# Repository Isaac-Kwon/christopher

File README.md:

# Project Christopher

앨런 튜링의 에니그마 해독기 **봄베(Bombe)** 를 재현하는 프로젝트.

소프트웨어 모델(Rust 코어 + Python 조작 인터페이스)에서 시작해 RTL, 실물까지 단계적으로 진행하고, LaTeX 보고서로 마무리한다.
재현 범위는 튜링-웰치먼 3로터 봄베와 해군 4로터(M4)까지다.

## 현재 상태

- **Phase 0 (기반): 완료.** 자료 조사, 배선표, 검증 벡터, 빌드 구성.
- **Phase 1 (소프트웨어): 동작.** 에니그마 I / M3 / M4, 메뉴 생성기, 3·4로터 봄베, 체킹 머신, 전체 탐색, Python 조작 인터페이스. 크립에서 평문까지 끝까지 해독한다.
- Phase 2 (RTL) 이후는 미착수.

전체 계획, 로드맵, 디렉토리 구조는 [docs/PLAN.md](docs/PLAN.md)에 있다.

## Quickstart

필요한 것: Rust 툴체인, Python 3.10 이상, [maturin](https://www.maturin.rs/).

### 빌드 출력 위치

이 저장소는 Dropbox 폴더 안에 있다. Dropbox가 `target/` 안의 파일을 잠가 빌드가 실패하는 문제가 실제로 발생했기 때문에, **빌드 출력과 Python 가상환경은 Dropbox 밖에 둔다.**

| 대상 | 위치 | 설정 |
|---|---|---|
| Cargo 빌드 출력 | `%LOCALAPPDATA%/christopher/target` | `.cargo/config.toml` (PC별 설정, git 제외) |
| Python 가상환경 | `%LOCALAPPDATA%/christopher/venv` | 수동 생성 |

프로젝트 폴더 안에는 가상환경을 만들지 않는다. 다른 PC에서는 `.cargo/config.toml`의 `target-dir`과 아래 경로를 그 PC에 맞게 바꾼다.

### 빌드

Python 바인딩을 가상환경에 설치한다 (Git Bash 기준, 저장소 루트에서 실행).

```bash
export VIRTUAL_ENV="$LOCALAPPDATA/christopher/venv"
$VIRTUAL_ENV/Scripts/maturin.exe develop --release
```

PowerShell에서는 `$env:VIRTUAL_ENV = "$env:LOCALAPPDATA/christopher/venv"` 뒤에 `& "$env:VIRTUAL_ENV/Scripts/maturin.exe" develop --release`.

### 시험

```bash
cargo test -p christopher-core
$VIRTUAL_ENV/Scripts/python.exe -m pytest tests
```

### 사용 예

암호문과 크립(추정 평문)에서 키와 평문을 복원한다.

```python
from christopher import Enigma, search

plain = "ANXOBERKOMMANDODERWEHRMACHTXWETTERVORHERSAGEFUERDIENORDSEEXHEUTEKLAR"
secret = Enigma("enigma-i", rotors=("III", "V", "II"), reflector="B", rings="GMC",
                positions="KDC", plugboard="AQ BZ CR DM EV FW GK HN IU JP")
cipher = secret.encrypt(plain)

# 크립 WETTERVORHERSAGEFUERDIE가 암호문의 28번째 글자(0부터)에서 시작한다고 보고 전체 로터 순서를 탐색
report = search(cipher, "WETTERVORHERSAGEFUERDIE", 28, model="enigma-i", max_edges=14)
print(report)                 # 120 wheel orders, 2109120 positions, ...
print(report.solutions[0])    # 로터 순서, 링, 시작 위치, 플러그보드, 평문
```

메뉴 작성 → 배선 → 구동 → 정지 확인 → 체킹을 단계별로 따라 하려면 노트북 [notebooks/01_crib_to_plaintext.ipynb](notebooks/01_crib_to_plaintext.ipynb)를 본다. 노트북 실행에는 `ipykernel`과 `matplotlib`이 필요하다(같은 가상환경에 설치).

M4 전체 탐색(로터 순서 1,344개, 약 6.1억 위치)의 예:

```bash
cargo run --release -p christopher-core --example full_search m4
```

## 문서

- [docs/PLAN.md](docs/PLAN.md) — 목표, 아키텍처, 로드맵, 디렉토리 구조
- [docs/reference/bombe-mechanics.md](docs/reference/bombe-mechanics.md) — 3로터 봄베의 기구와 동작 (출처 포함)
- [docs/reference/four-rotor-and-relay-bombes.md](docs/reference/four-rotor-and-relay-bombes.md) — 4로터 봄베와 릴레이식 봄베
- [report/references.bib](report/references.bib) — 참고문헌

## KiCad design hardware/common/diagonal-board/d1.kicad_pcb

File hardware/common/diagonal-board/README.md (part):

# Diagonal board, five boards (common part)

Generated KiCad 10 schematics and **placement-only** PCBs of Welchman's diagonal board, split in five boards as decided in
`docs/decisions/0002-gear-detail-decisions.md` section 9 and `hardware/common/diagonal-board.md`; connector rules from
`docs/decisions/0003-interfaces.md` (5.1 gender, 5.2 pins, 7 grounding/CHASSIS). The letter jacks live on these boards
(design brief 4.3/4.4); everything else of the menu panel is on `hardware/common/patch-panel`. Build products of the scripts, do not edit by hand.

## Design

| Board | Letters (jack columns: upper / lower) | Jacks | Junction headers | Size (placed) | Left edge on the panel |
|---|---|---:|---|---|---:|
| D1 | A B C / N O P | 12 | 3 right (edge) | 331.6 x 130 | 17.8 |
| D2 | D E F / Q R S | 12 | 3 left (gap col 1-2), 3 right (edge) | 327.6 x 130 | 351.8 |
| D3 | G H I / T U V | 12 | 3 left (gap col 1-2), 3 right (edge) | 327.6 x 130 | 681.8 |
| D4 | J K / W X | 8 | 3 left (gap col 1-2), 3 right (edge) | 217.6 x 130 | 1,011.8 |
| D5 | L M / Y Z | 8 | 3 left (gap col 1-2) | 190.5 x 130 | 1,231.8 |

Panel x is measured from the left end of the 1,440 mm bank span (`hardware/gear/layout.md` 3.9/3.10; the relay machine's panel is the
same). The five boards cover 17.8 ... 1,422.2 (1,404.5 mm, 2.4 mm air between boards, 17.8 mm free at each end).

* **Letter jack** (2 per letter, 52 in all): male D-sub 37 (`DSUB-37_Pins_Vertical..._MountingHoles`, shells through the panel), pins 1-26 =
  wire A..Z of the letter's cable, **27-29 = 0 V reference tied here** (common side), 30-37 not connected, shell pads = `CHASSIS`. The
  two jacks of a letter are in parallel (all 26 lines). Panel order as in `layout.md` 3.10: **one 13 x 4 grid at 110 x 30 mm over all
  five boards** (the 110 mm column pitch also holds across a board boundary), column centres at 60 + 110 j (j = 0..12) from the left end of
  the bank span, upper letter's two jacks in rows 1-2, lower letter's in rows 3-4. The grid is 1,390.5 mm wide (jack courtyards).
* **Diagonal links:** wire w of letter c <-> wire c of letter w; 325 link nets `L_XY` (X < Y) with four jack pins each (2 jacks of X, 2 of Y),
  26 self nets `S_X` (the own wire, two pins, linked to nothing).
* **Junctions:** per boundary 3 x 64-pin IDC headers (2 x 32, 2.54): `XRn` on the right edge of board k, `XLn` on the left edge of board k+1
  (n = 1..3), 64-way flat cable, pin p to pin p of the same n. The links crossing the boundary are sorted by (X, Y); link i takes connector
  i // 64 + 1, pin i % 64 + 1; a link passing over a board joins its left and right header pin. Crossing links per boundary k(26-k):
  **120 / 168 / 144 / 88** (verified); junction pins spare: 68 / 20 / 44 / 100 after reserving **connector 3, pins 61-64 for the 0 V reference**
  (each boundary, all four pins). Headers are on the **back**, vertical, pin 1 at the top, identical orientation on every board, three side by side (pitch 10.8).
* **Where the headers sit (staggered).** A block of three headers is 31.6 mm wide; the gap between two jack columns is 39.5 mm, so only
  ONE block fits into a gap. At each boundary, `XR1..XR3` of board k fill the boundary gap at the right edge of board k (XR1 nearest the edge);
  `XL1..XL3` of board k+1 sit in the gap between its jack columns 1 and 2 (XL1 nearest the boundary). The three ribbons of a boundary
  therefore **nest** (XR1-XL1 innermost; pin-1 spans 91.4 / 113.0 / 134.6 mm) and pass over the back of the first jack column of board k+1.
  Ribbon length about 150-200 mm (to be measured with real sockets). The earlier layout (both blocks at the edges, XR1 and XL1 both on the
  left of their blocks) would also have crossed the ribbons: equal spans shifted by 10.8 mm cannot be laid as flat U-loops.
* **Grounding:** one `GND` net per board, joined across boards by the four 0 V junction pins; `J0V` (2-pole 5.08 terminal, both pins one net) on D1 is the single
  connection to the 0 V of the power supply (the patch panel has the other `J0V`: connect both to the same 0 V point, never to PE). Each board has `CHASSIS` (shells + M3
  mounting holes with plated pads) tied to 0 V only through 1 Mohm || 10 nF (R1, C1; decision 0003 7.1).
* 4 layers (routing density 168 through-nets over D2/D3; the user routes), 4 or 6 M3 holes.

## Files

| File | Purpose |
|---|---|
| `ki_common.py` | shared library (identical copy in `gear/contact-board` and `common/patch-panel`) |
| `gen_diagonal.py` | letters + 325 links + junction pin assignment -> `d1..d5.kicad_pro/.kicad_sch` |
| `gen_diagonal_pcb.py` | placement -> `d1..d5.kicad_pcb` (netlist via kicad-cli), board positions on the panel (`panel_offsets`), kicad-cli helpers |
| `verify_diagonal.py` | composes the five netlists through the junction ribbons and checks the diagonal board, with negative tests |
| `verify_diagonal_pcb.py` | ERC, board vs schematic, DRC, geometry (pcbnew), the five boards on the panel (one jack grid, ribbons), determinism, negative tests |

    python gen_diagonal.py && python gen_diagonal_pcb.py
    python verify_diagonal.py && python verify_diagonal_pcb.py        # the PCB check takes a few minutes (kicad-cli, 5 boards)

KiCad 10 at `C:/Program Files/KiCad/10.0` (or `KICAD_SHARE`, `KICAD_CLI`); build output in `%LOCALAPPDATA%/christopher/diagonal-board`.
kicad-cli and pcbnew run on copies in `<build>/stage` with a timeout (it sometimes hangs on the synced work folder, and leaves
`.kicad_prl`/lock files next to the file it opens).

## Results (KiCad 10.0.4)

| Item | Result |
|---|---|
| ERC (all severities) | d1..d5: 0 violations |
| Parts | D1 24 (12 jacks, 3 headers, J0V, R1, C1, 6 holes), D2 26, D3 26, D4 20, D5 17 |
| Composition (independent of the generator's net names) | letters 6/6/6/4/4; **325 link nets, each exactly four jack pins**, 26 self nets of two pins; no other jack-pin connection; pins 27-29 of all 52 jacks on one 0 V net (with `J0V`, one RC per board); five CHASSIS nets, not shorted to 0 V; junction use 120/168/144/88 |
| Negative tests | swapped wires on a jack, wire <-> 0 V pin on a jack, two junction pins swapped (near and far side), signal <-> 0 V junction pin swapped, missing ribbon (signal connectors), missing 0 V ribbon: all detected |
| Placement DRC | **0 violations** on all five; unconnected = ratsnest (D1 365, D2 451, D3 463, D4 324, D5 248; pcbnew count = sum(pads-1)); pad nets = schematic (IPC-D-356); jacks on the 110 x 30 grid, headers on the back, pin 1 at the top, same pin-1 height at both ends of every ribbon; negative test (swapped pad nets) detected |
| Panel (five boards together) | jack column pitch 110.00 over all 13 columns (also across the 4 boundaries), first column centre 60.00; boards 17.7 ... 1,422.3 of the 1,440 bank span (outline incl. line width), air 2.3 between boards, longest 331.7 <= 350; the ribbons of every boundary nest, pin-1 spans 91.4 / 113.0 / 134.6 mm; negative tests (a board shifted 1 mm, two headers of a block exchanged, a board 30 mm longer, all boards 15 mm to the right) detected |
| Determinism | schematics and boards regenerate byte-identical |

## Open questions / deviations from the concept documents

1. **Panel pitch and board size (resolved 2026-11-16).** The first placement put both header blocks of a boundary at the board edges; two blocks
   (2 x 32 mm) do not fit into the 39.5 mm gap between two jack columns, so the jacks of neighbouring boards were 149.3 mm apart and the five boards
   1,561.7 mm long, 121.7 mm more than the 1,440 mm bank span (they ran into the control area, where the power-unit plate also sits). Now the blocks
   are staggered (section Design): every gap holds at most one block, the 110 mm pitch holds everywhere, the boards are 1,404.5 mm in all and fit the
   bank span with 17.8 mm at each end, and the longest board is 331.6 mm (`layout.md`: at most 350). Height 130 unchanged. Alternatives that were
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
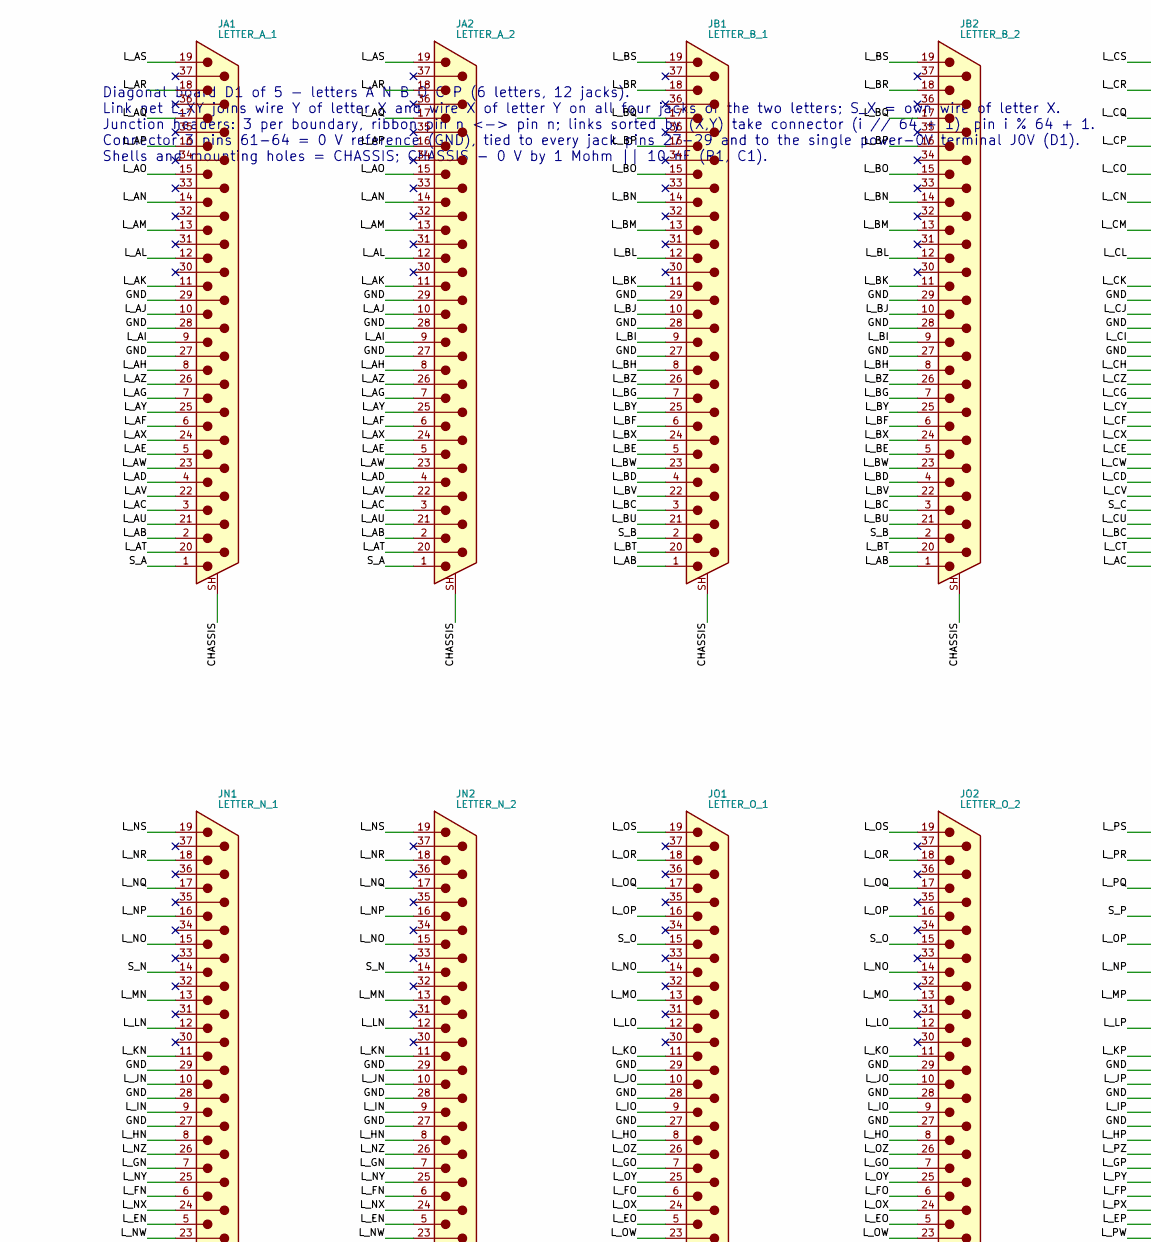
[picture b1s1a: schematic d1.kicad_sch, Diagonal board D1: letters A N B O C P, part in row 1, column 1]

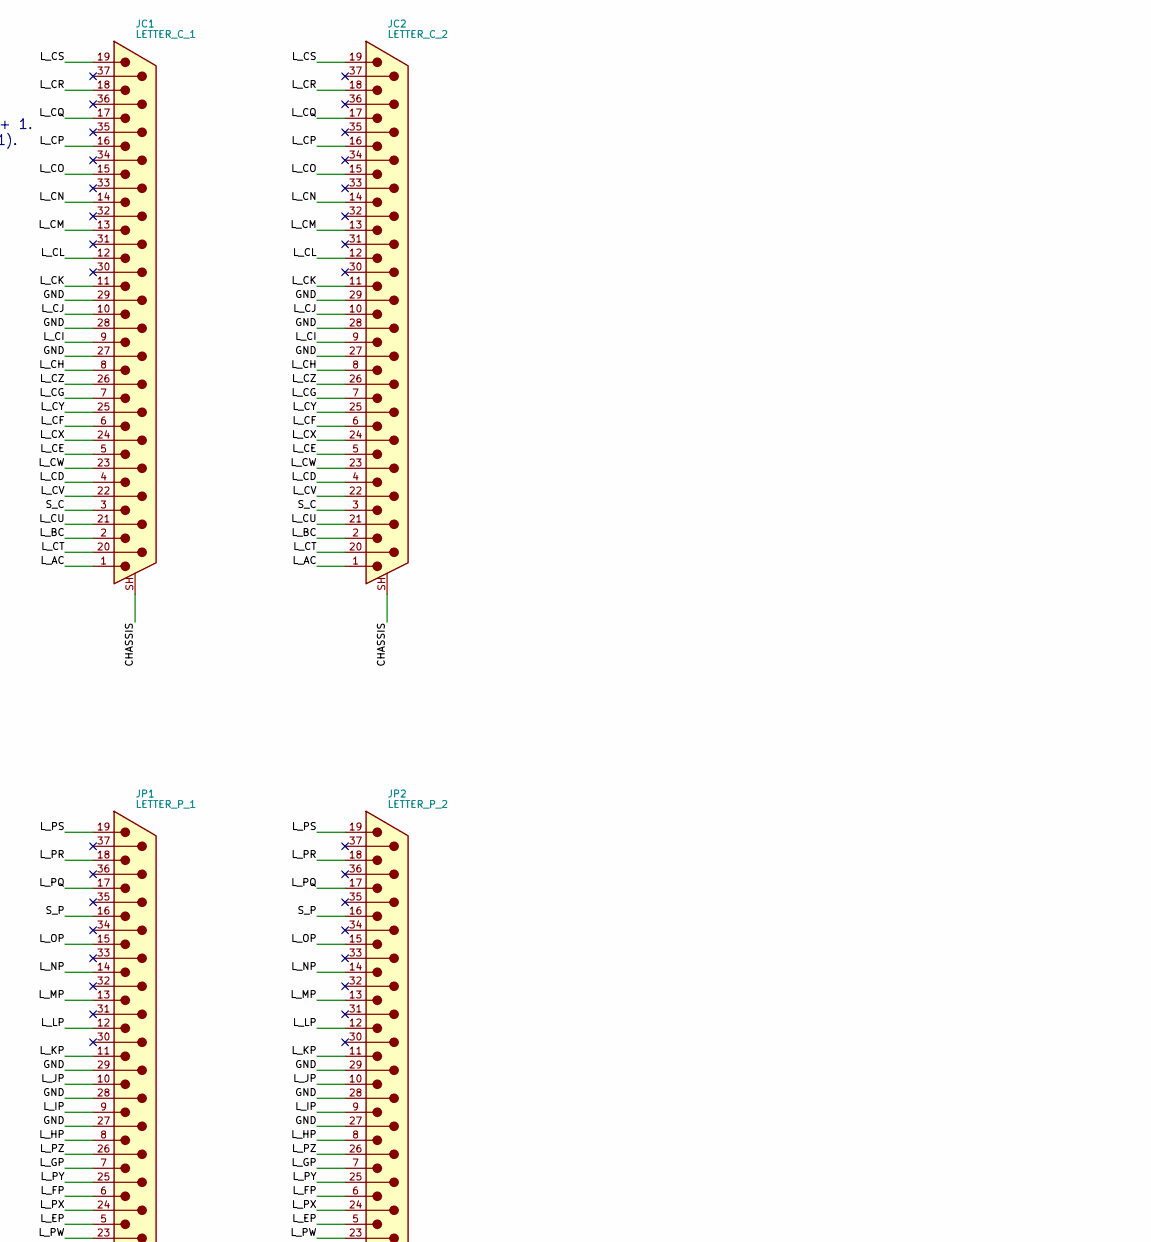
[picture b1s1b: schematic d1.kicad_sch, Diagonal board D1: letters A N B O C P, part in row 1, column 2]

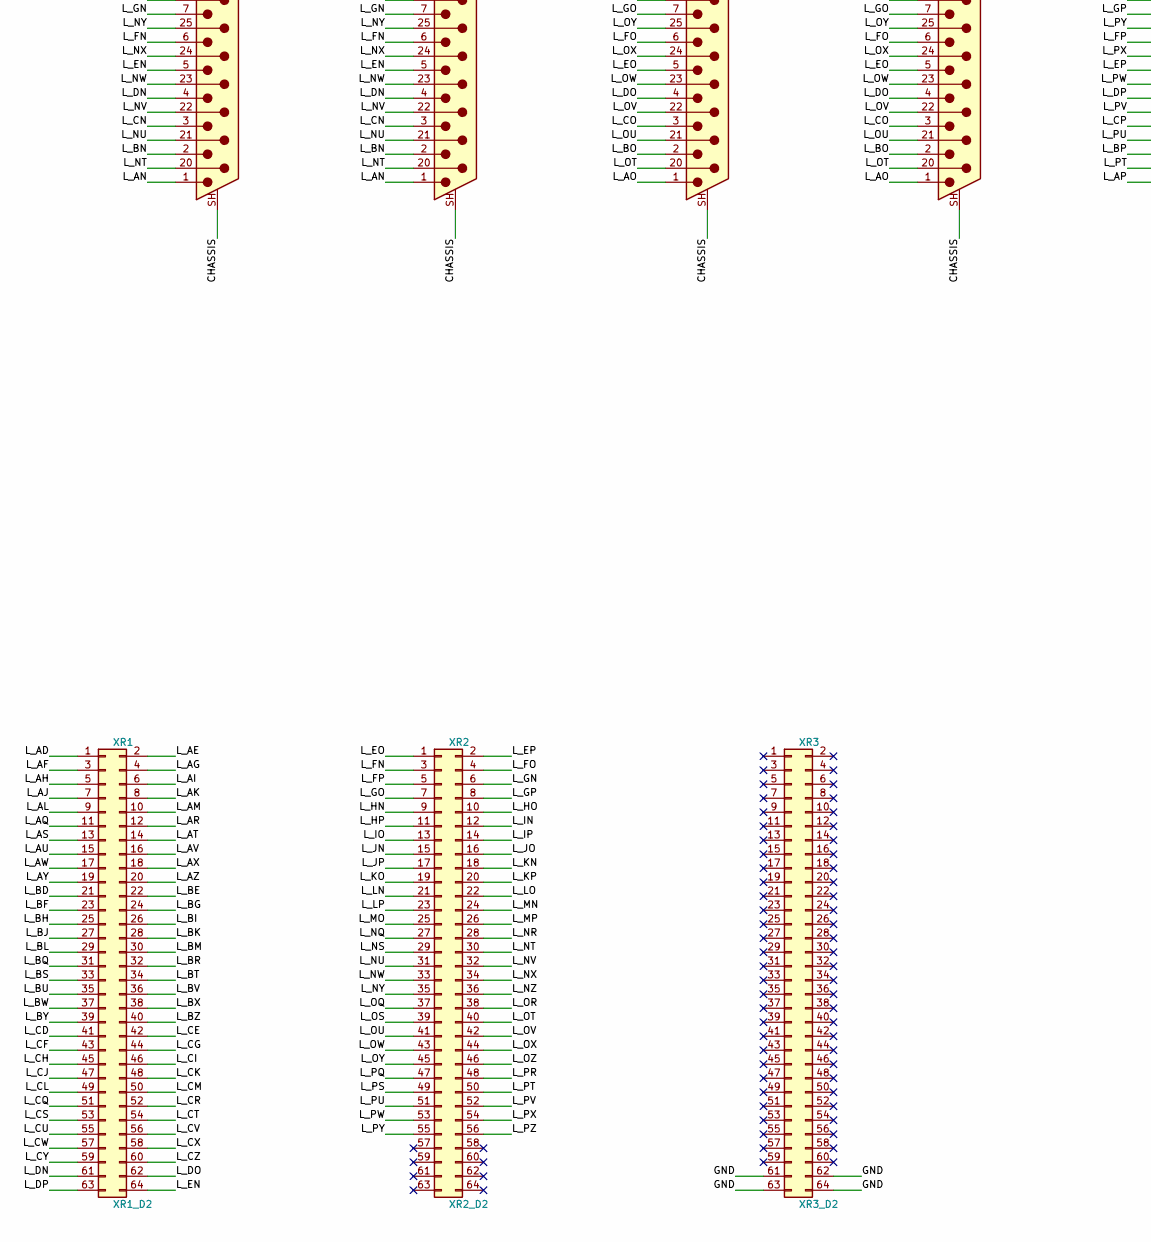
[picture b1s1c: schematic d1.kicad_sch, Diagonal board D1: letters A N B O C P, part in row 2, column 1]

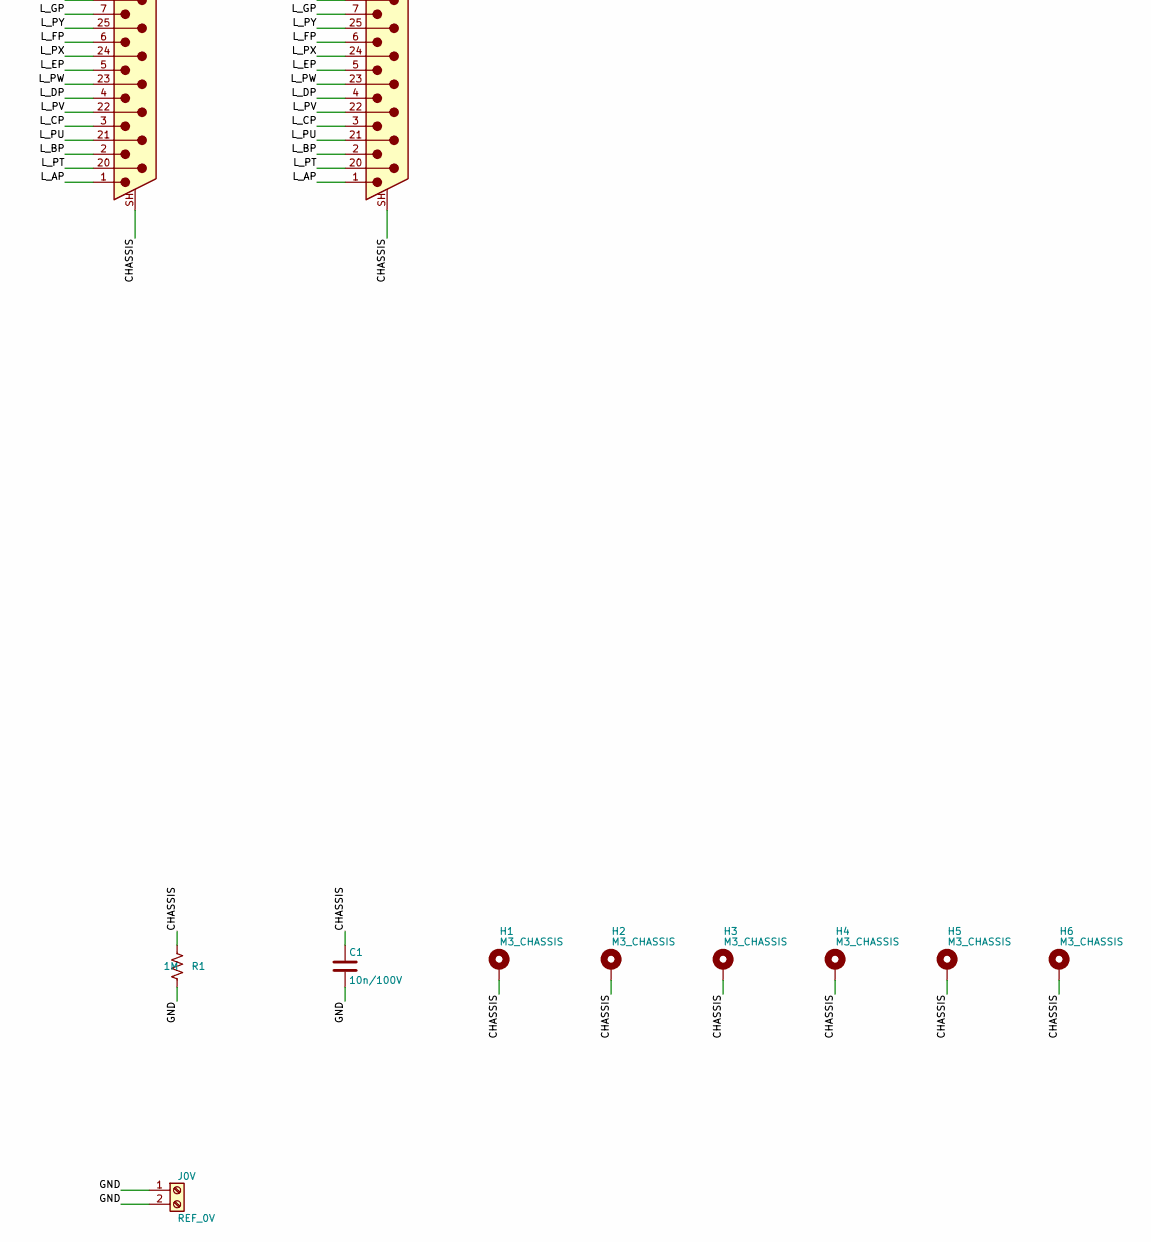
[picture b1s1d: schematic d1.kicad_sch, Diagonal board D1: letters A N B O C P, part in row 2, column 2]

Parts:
C1: 10n/100V; C_0805_2012Metric
H1, H2, H3, H4, H5, H6: M3_CHASSIS; MountingHole_3.2mm_M3_Pad
J0V: REF_0V; TerminalBlock_Phoenix_MKDS-1,5-2-5.08_1x02_P5.08mm_Horizont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
JA1: LETTER_A_1; DSUB-37_Pins_Vertical_P2.77x2.84mm_MountingHoles
JA2: LETTER_A_2; DSUB-37_Pins_Vertical_P2.77x2.84mm_MountingHoles
JB1: LETTER_B_1; DSUB-37_Pins_Vertical_P2.77x2.84mm_MountingHoles
JB2: LETTER_B_2; DSUB-37_Pins_Vertical_P2.77x2.84mm_MountingHoles
JC1: LETTER_C_1; DSUB-37_Pins_Vertical_P2.77x2.84mm_MountingHoles
JC2: LETTER_C_2; DSUB-37_Pins_Vertical_P2.77x2.84mm_MountingHoles
JN1: LETTER_N_1; DSUB-37_Pins_Vertical_P2.77x2.84mm_MountingHoles
JN2: LETTER_N_2; DSUB-37_Pins_Vertical_P2.77x2.84mm_MountingHoles
JO1: LETTER_O_1; DSUB-37_Pins_Vertical_P2.77x2.84mm_MountingHoles
JO2: LETTER_O_2; DSUB-37_Pins_Vertical_P2.77x2.84mm_MountingHoles
JP1: LETTER_P_1; DSUB-37_Pins_Vertical_P2.77x2.84mm_MountingHoles
JP2: LETTER_P_2; DSUB-37_Pins_Vertical_P2.77x2.84mm_MountingHoles
R1: 1M; R_0603_1608Metric
XR1: XR1_D2; IDC-Header_2x32_P2.54mm_Vertical
XR2: XR2_D2; IDC-Header_2x32_P2.54mm_Vertical
XR3: XR3_D2; IDC-Header_2x32_P2.54mm_Vertical

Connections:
/CHASSIS: C1.1, H1.1, H2.1, H3.1, H4.1, H5.1, H6.1, JA1.SH (PAD), JA2.SH (PAD), JB1.SH (PAD), JB2.SH (PAD), JC1.SH (PAD), JC2.SH (PAD), JN1.SH (PAD), JN2.SH (PAD), JO1.SH (PAD), JO2.SH (PAD), JP1.SH (PAD), JP2.SH (PAD), R1.1
/GND: C1.2, J0V.1, J0V.2, JA1.27, JA1.28, JA1.29, JA2.27, JA2.28, JA2.29, JB1.27, JB1.28, JB1.29, JB2.27, JB2.28, JB2.29, JC1.27, JC1.28, JC1.29, JC2.27, JC2.28, JC2.29, JN1.27, JN1.28, JN1.29, JN2.27, JN2.28, JN2.29, JO1.27, JO1.28, JO1.29, JO2.27, JO2.28, JO2.29, JP1.27, JP1.28, JP1.29, JP2.27, JP2.28, JP2.29, R1.2, XR3.61, XR3.62, XR3.63, XR3.64
/L_AB: JA1.2, JA2.2, JB1.1, JB2.1
/L_AC: JA1.3, JA2.3, JC1.1, JC2.1
/L_AD: JA1.4, JA2.4, XR1.1
/L_AE: JA1.5, JA2.5, XR1.2
/L_AF: JA1.6, JA2.6, XR1.3
/L_AG: JA1.7, JA2.7, XR1.4
/L_AH: JA1.8, JA2.8, XR1.5
/L_AI: JA1.9, JA2.9, XR1.6
/L_AJ: JA1.10, JA2.10, XR1.7
/L_AK: JA1.11, JA2.11, XR1.8
/L_AL: JA1.12, JA2.12, XR1.9
/L_AM: JA1.13, JA2.13, XR1.10
/L_AN: JA1.14, JA2.14, JN1.1, JN2.1
/L_AO: JA1.15, JA2.15, JO1.1, JO2.1
/L_AP: JA1.16, JA2.16, JP1.1, JP2.1
/L_AQ: JA1.17, JA2.17, XR1.11
/L_AR: JA1.18, JA2.18, XR1.12
/L_AS: JA1.19, JA2.19, XR1.13
/L_AT: JA1.20, JA2.20, XR1.14
/L_AU: JA1.21, JA2.21, XR1.15
/L_AV: JA1.22, JA2.22, XR1.16
/L_AW: JA1.23, JA2.23, XR1.17
/L_AX: JA1.24, JA2.24, XR1.18
/L_AY: JA1.25, JA2.25, XR1.19
/L_AZ: JA1.26, JA2.26, XR1.20
/L_BC: JB1.3, JB2.3, JC1.2, JC2.2
/L_BD: JB1.4, JB2.4, XR1.21
/L_BE: JB1.5, JB2.5, XR1.22
/L_BF: JB1.6, JB2.6, XR1.23
/L_BG: JB1.7, JB2.7, XR1.24
/L_BH: JB1.8, JB2.8, XR1.25
/L_BI: JB1.9, JB2.9, XR1.26
/L_BJ: JB1.10, JB2.10, XR1.27
/L_BK: JB1.11, JB2.11, XR1.28
/L_BL: JB1.12, JB2.12, XR1.29
/L_BM: JB1.13, JB2.13, XR1.30
/L_BN: JB1.14, JB2.14, JN1.2, JN2.2
/L_BO: JB1.15, JB2.15, JO1.2, JO2.2
/L_BP: JB1.16, JB2.16, JP1.2, JP2.2
/L_BQ: JB1.17, JB2.17, XR1.31
/L_BR: JB1.18, JB2.18, XR1.32
/L_BS: JB1.19, JB2.19, XR1.33
/L_BT: JB1.20, JB2.20, XR1.34
/L_BU: JB1.21, JB2.21, XR1.35
/L_BV: JB1.22, JB2.22, XR1.36
/L_BW: JB1.23, JB2.23, XR1.37
/L_BX: JB1.24, JB2.24, XR1.38
/L_BY: JB1.25, JB2.25, XR1.39
/L_BZ: JB1.26, JB2.26, XR1.40
/L_CD: JC1.4, JC2.4, XR1.41
/L_CE: JC1.5, JC2.5, XR1.42
/L_CF: JC1.6, JC2.6, XR1.43
/L_CG: JC1.7, JC2.7, XR1.44
/L_CH: JC1.8, JC2.8, XR1.45
/L_CI: JC1.9, JC2.9, XR1.46
/L_CJ: JC1.10, JC2.10, XR1.47
/L_CK: JC1.11, JC2.11, XR1.48
/L_CL: JC1.12, JC2.12, XR1.49
/L_CM: JC1.13, JC2.13, XR1.50
/L_CN: JC1.14, JC2.14, JN1.3, JN2.3
/L_CO: JC1.15, JC2.15, JO1.3, JO2.3
/L_CP: JC1.16, JC2.16, JP1.3, JP2.3
/L_CQ: JC1.17, JC2.17, XR1.51
/L_CR: JC1.18, JC2.18, XR1.52
/L_CS: JC1.19, JC2.19, XR1.53
/L_CT: JC1.20, JC2.20, XR1.54
/L_CU: JC1.21, JC2.21, XR1.55
/L_CV: JC1.22, JC2.22, XR1.56
/L_CW: JC1.23, JC2.23, XR1.57
/L_CX: JC1.24, JC2.24, XR1.58
/L_CY: JC1.25, JC2.25, XR1.59
/L_CZ: JC1.26, JC2.26, XR1.60
/L_DN: JN1.4, JN2.4, XR1.61
/L_DO: JO1.4, JO2.4, XR1.62
/L_DP: JP1.4, JP2.4, XR1.63
/L_EN: JN1.5, JN2.5, XR1.64
/L_EO: JO1.5, JO2.5, XR2.1
/L_EP: JP1.5, JP2.5, XR2.2
/L_FN: JN1.6, JN2.6, XR2.3
/L_FO: JO1.6, JO2.6, XR2.4
/L_FP: JP1.6, JP2.6, XR2.5
/L_GN: JN1.7, JN2.7, XR2.6
/L_GO: JO1.7, JO2.7, XR2.7
/L_GP: JP1.7, JP2.7, XR2.8
/L_HN: JN1.8, JN2.8, XR2.9
/L_HO: JO1.8, JO2.8, XR2.10
/L_HP: JP1.8, JP2.8, XR2.11
/L_IN: JN1.9, JN2.9, XR2.12
/L_IO: JO1.9, JO2.9, XR2.13
/L_IP: JP1.9, JP2.9, XR2.14
/L_JN: JN1.10, JN2.10, XR2.15
/L_JO: JO1.10, JO2.10, XR2.16
/L_JP: JP1.10, JP2.10, XR2.17
/L_KN: JN1.11, JN2.11, XR2.18
/L_KO: JO1.11, JO2.11, XR2.19
/L_KP: JP1.11, JP2.11, XR2.20
/L_LN: JN1.12, JN2.12, XR2.21
/L_LO: JO1.12, JO2.12, XR2.22
/L_LP: JP1.12, JP2.12, XR2.23
/L_MN: JN1.13, JN2.13, XR2.24
/L_MO: JO1.13, JO2.13, XR2.25
/L_MP: JP1.13, JP2.13, XR2.26
/L_NO: JN1.15, JN2.15, JO1.14, JO2.14
/L_NP: JN1.16, JN2.16, JP1.14, JP2.14
/L_NQ: JN1.17, JN2.17, XR2.27
/L_NR: JN1.18, JN2.18, XR2.28
/L_NS: JN1.19, JN2.19, XR2.29
/L_NT: JN1.20, JN2.20, XR2.30
/L_NU: JN1.21, JN2.21, XR2.31
/L_NV: JN1.22, JN2.22, XR2.32
/L_NW: JN1.23, JN2.23, XR2.33
/L_NX: JN1.24, JN2.24, XR2.34
/L_NY: JN1.25, JN2.25, XR2.35
/L_NZ: JN1.26, JN2.26, XR2.36
/L_OP: JO1.16, JO2.16, JP1.15, JP2.15
/L_OQ: JO1.17, JO2.17, XR2.37
/L_OR: JO1.18, JO2.18, XR2.38
/L_OS: JO1.19, JO2.19, XR2.39
/L_OT: JO1.20, JO2.20, XR2.40
/L_OU: JO1.21, JO2.21, XR2.41
/L_OV: JO1.22, JO2.22, XR2.42
/L_OW: JO1.23, JO2.23, XR2.43
/L_OX: JO1.24, JO2.24, XR2.44
/L_OY: JO1.25, JO2.25, XR2.45
/L_OZ: JO1.26, JO2.26, XR2.46
/L_PQ: JP1.17, JP2.17, XR2.47
/L_PR: JP1.18, JP2.18, XR2.48
/L_PS: JP1.19, JP2.19, XR2.49
/L_PT: JP1.20, JP2.20, XR2.50
/L_PU: JP1.21, JP2.21, XR2.51
/L_PV: JP1.22, JP2.22, XR2.52
/L_PW: JP1.23, JP2.23, XR2.53
/L_PX: JP1.24, JP2.24, XR2.54
/L_PY: JP1.25, JP2.25, XR2.55
/L_PZ: JP1.26, JP2.26, XR2.56
/S_A: JA1.1, JA2.1
/S_B: JB1.2, JB2.2
/S_C: JC1.3, JC2.3
/S_N: JN1.14, JN2.14
/S_O: JO1.15, JO2.15
/S_P: JP1.16, JP2.16

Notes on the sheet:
Diagonal board D1 of 5 - letters A N B O C P (6 letters, 12 jacks). Link net L_XY joins wire Y of letter X and wire X of letter Y on all four jacks of the two letters; S_X = own wire of letter X. Junction headers: 3 per boundary, ribbon pin n <-> pin n; links sorted by (X,Y) take connector (i // 64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

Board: 4 copper layers, 24 parts (3 on the bottom side), 143 nets, no tracks yet.

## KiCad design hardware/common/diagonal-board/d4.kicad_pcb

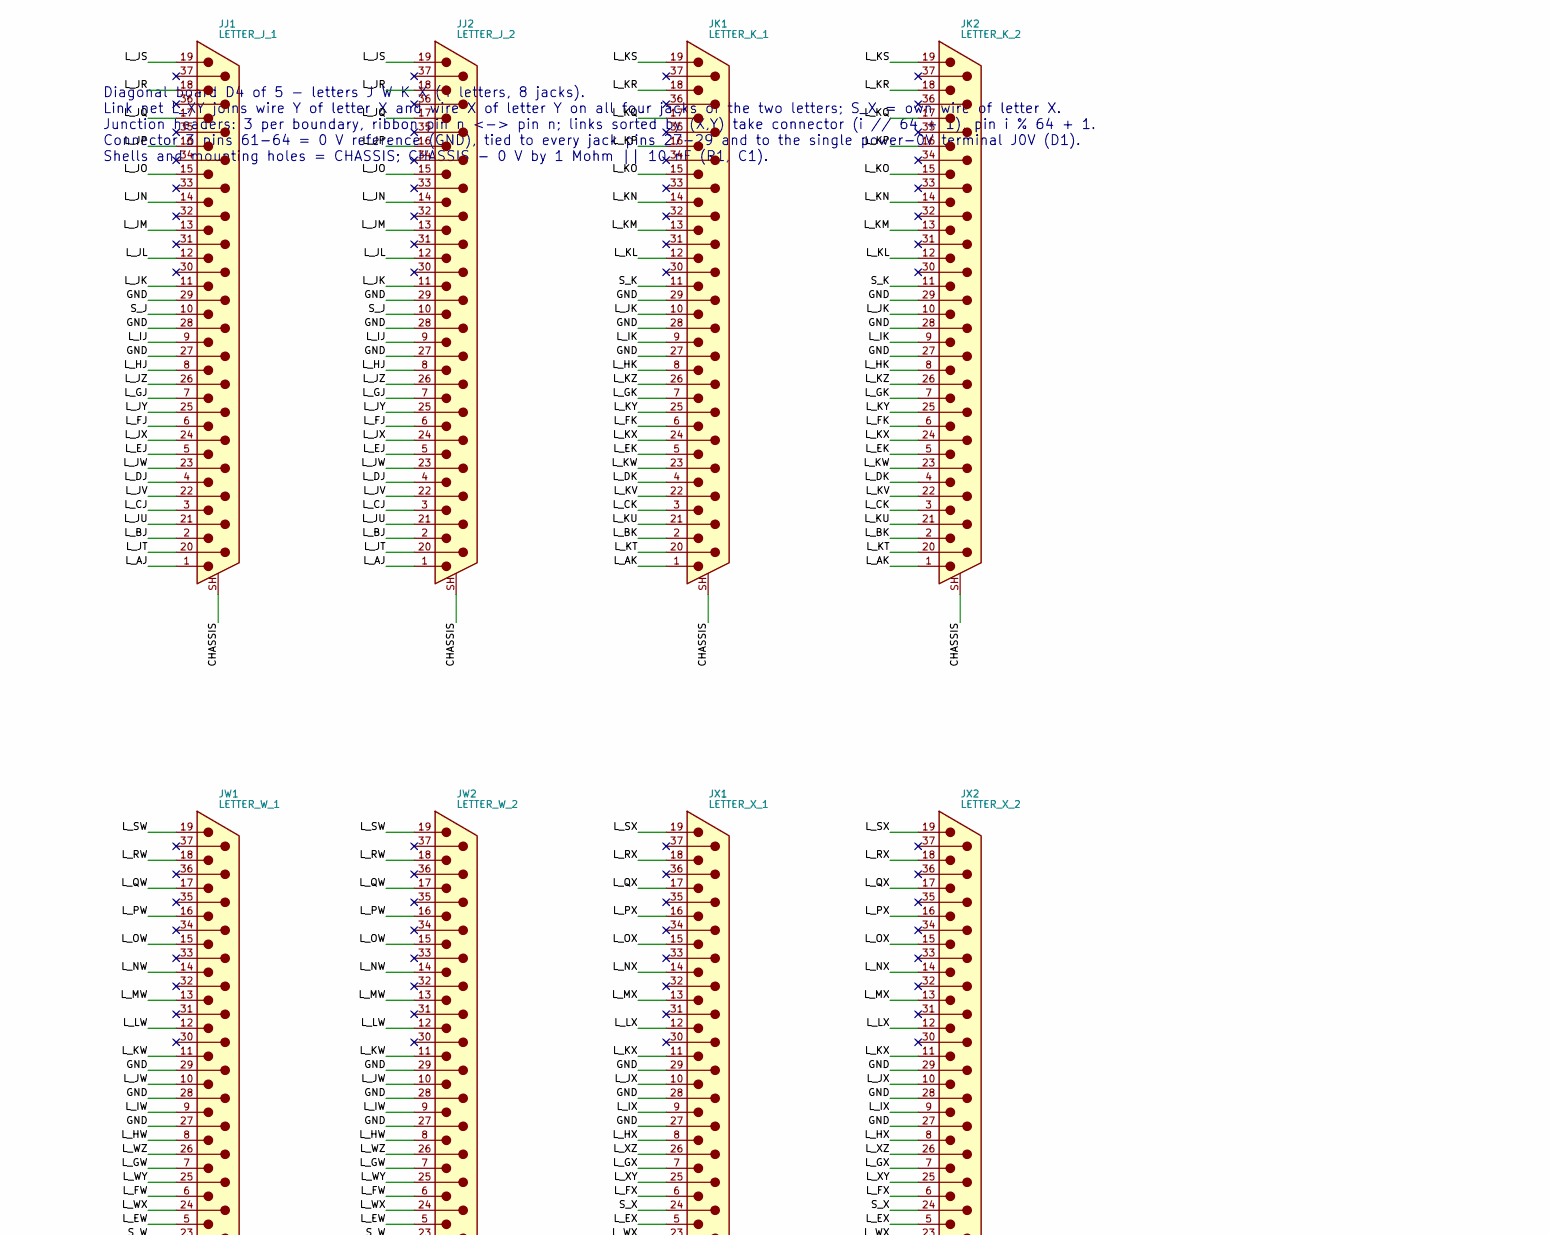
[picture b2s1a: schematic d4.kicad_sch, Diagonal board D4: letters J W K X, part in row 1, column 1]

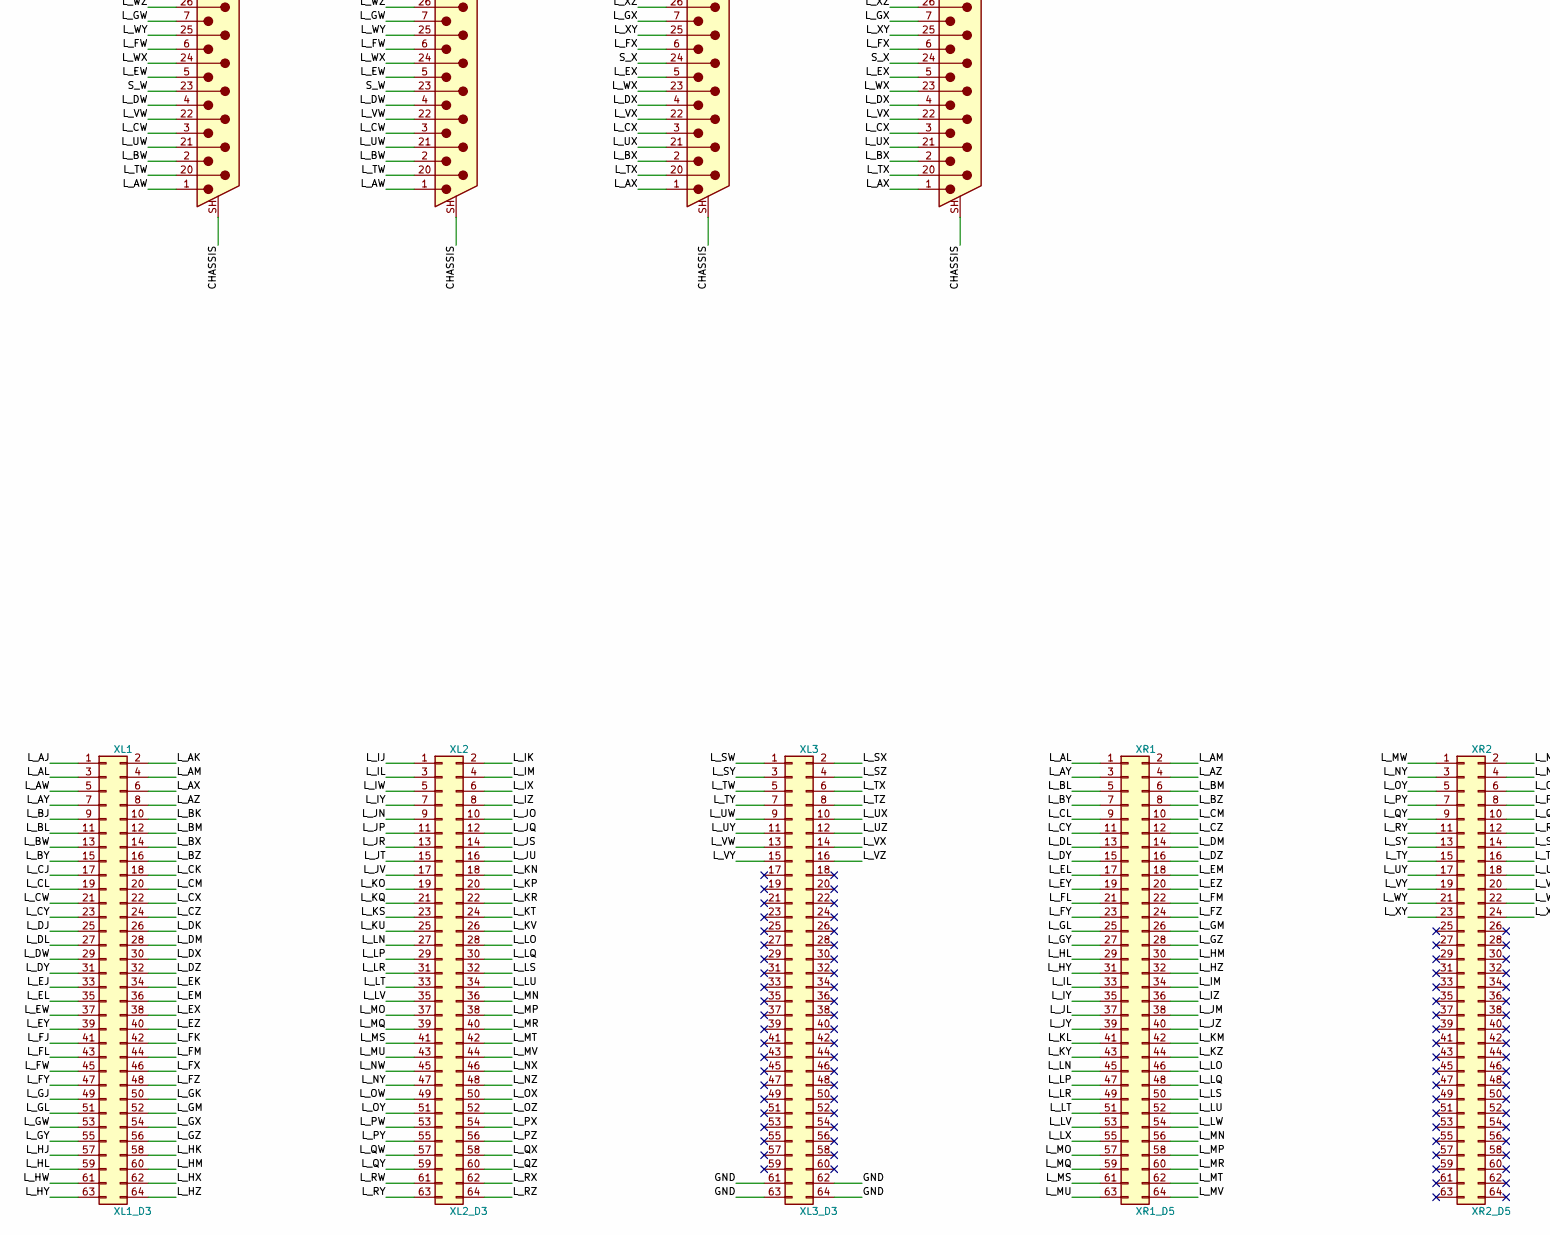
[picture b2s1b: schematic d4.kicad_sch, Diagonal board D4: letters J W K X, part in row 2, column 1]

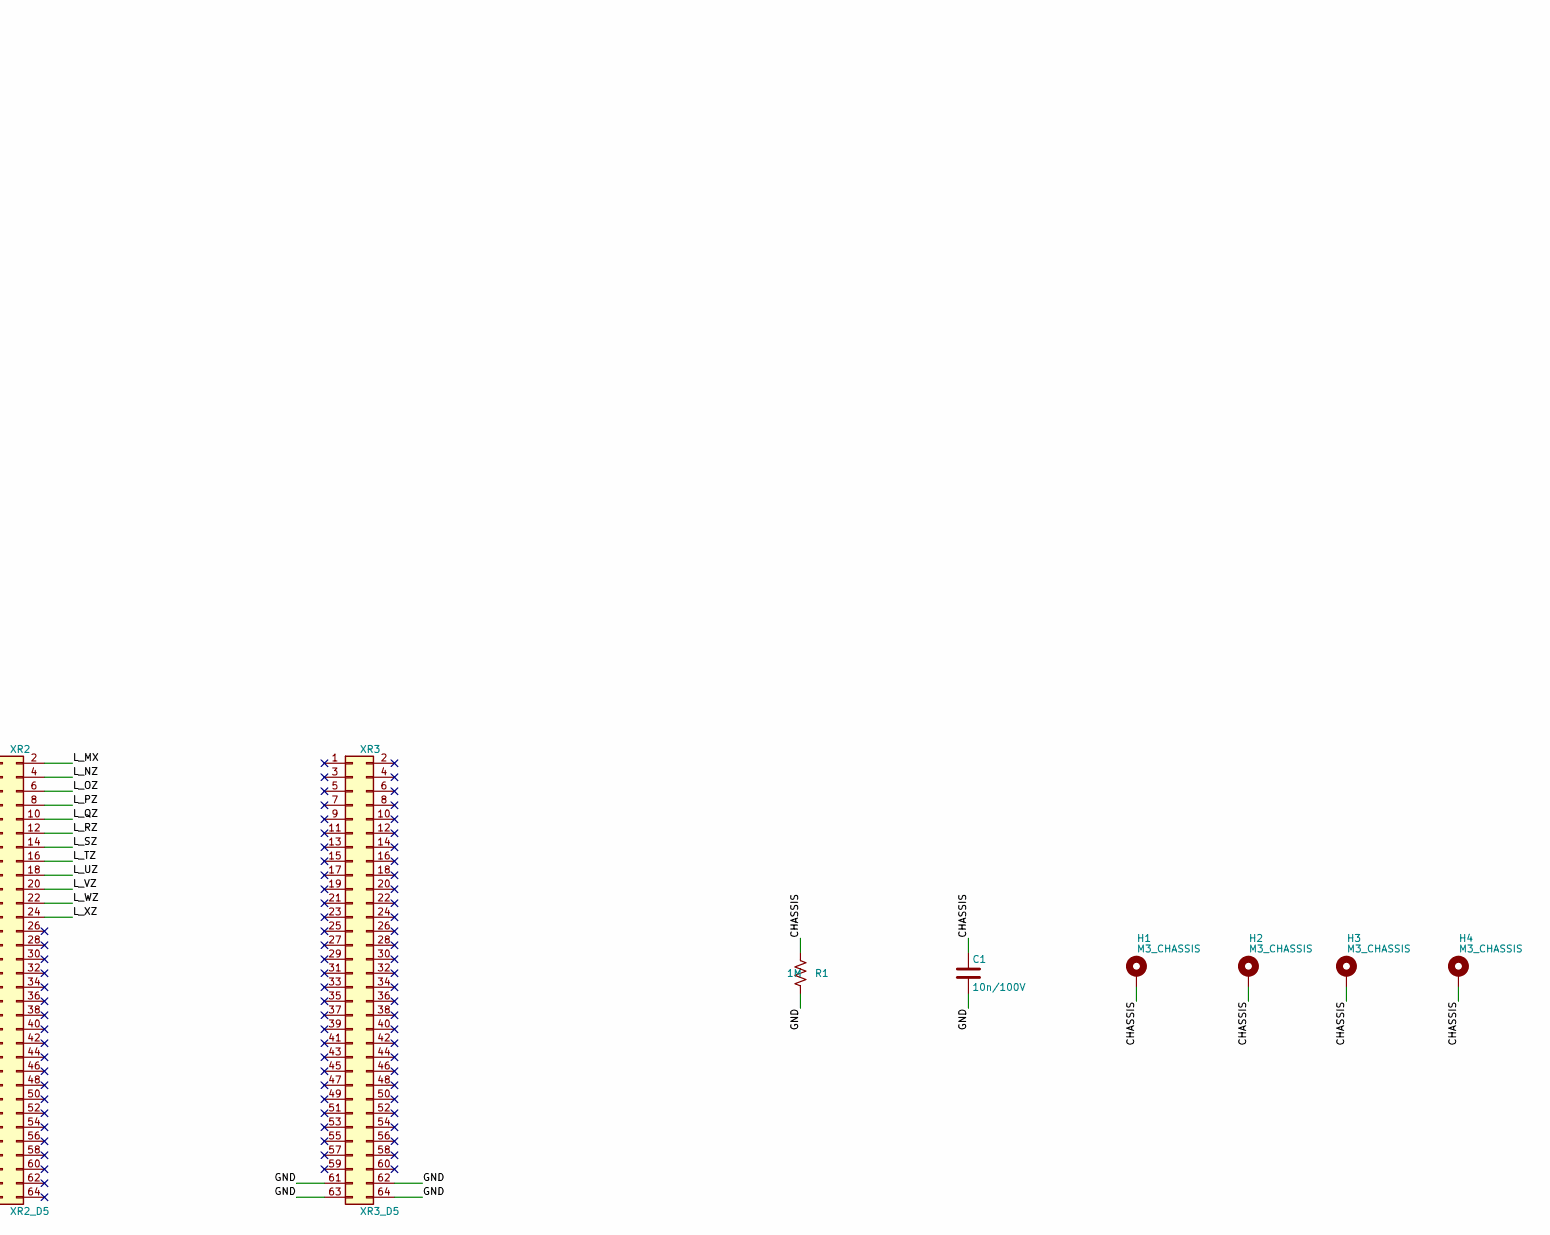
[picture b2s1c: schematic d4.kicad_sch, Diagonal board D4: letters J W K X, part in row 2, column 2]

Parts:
C1: 10n/100V; C_0805_2012Metric
H1, H2, H3, H4: M3_CHASSIS; MountingHole_3.2mm_M3_Pad
JJ1: LETTER_J_1; DSUB-37_Pins_Vertical_P2.77x2.84mm_MountingHoles
JJ2: LETTER_J_2; DSUB-37_Pins_Vertical_P2.77x2.84mm_MountingHoles
JK1: LETTER_K_1; DSUB-37_Pins_Vertical_P2.77x2.84mm_MountingHoles
JK2: LETTER_K_2; DSUB-37_Pins_Vertical_P2.77x2.84mm_MountingHoles
JW1: LETTER_W_1; DSUB-37_Pins_Vertical_P2.77x2.84mm_MountingHoles
JW2: LETTER_W_2; DSUB-37_Pins_Vertical_P2.77x2.84mm_MountingHoles
JX1: LETTER_X_1; DSUB-37_Pins_Vertical_P2.77x2.84mm_MountingHoles
JX2: LETTER_X_2; DSUB-37_Pins_Vertical_P2.77x2.84mm_MountingHoles
R1: 1M; R_0603_1608Metric
XL1: XL1_D3; IDC-Header_2x32_P2.54mm_Vertical
XL2: XL2_D3; IDC-Header_2x32_P2.54mm_Vertical
XL3: XL3_D3; IDC-Header_2x32_P2.54mm_Vertical
XR1: XR1_D5; IDC-Header_2x32_P2.54mm_Vertical
XR2: XR2_D5; IDC-Header_2x32_P2.54mm_Vertical
XR3: XR3_D5; IDC-Header_2x32_P2.54mm_Vertical

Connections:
/CHASSIS: C1.1, H1.1, H2.1, H3.1, H4.1, JJ1.SH (PAD), JJ2.SH (PAD), JK1.SH (PAD), JK2.SH (PAD), JW1.SH (PAD), JW2.SH (PAD), JX1.SH (PAD), JX2.SH (PAD), R1.1
/GND: C1.2, JJ1.27, JJ1.28, JJ1.29, JJ2.27, JJ2.28, JJ2.29, JK1.27, JK1.28, JK1.29, JK2.27, JK2.28, JK2.29, JW1.27, JW1.28, JW1.29, JW2.27, JW2.28, JW2.29, JX1.27, JX1.28, JX1.29, JX2.27, JX2.28, JX2.29, R1.2, XL3.61, XL3.62, XL3.63, XL3.64, XR3.61, XR3.62, XR3.63, XR3.64
/L_AJ: JJ1.1, JJ2.1, XL1.1
/L_AK: JK1.1, JK2.1, XL1.2
/L_AL: XL1.3, XR1.1
/L_AM: XL1.4, XR1.2
/L_AW: JW1.1, JW2.1, XL1.5
/L_AX: JX1.1, JX2.1, XL1.6
/L_AY: XL1.7, XR1.3
/L_AZ: XL1.8, XR1.4
/L_BJ: JJ1.2, JJ2.2, XL1.9
/L_BK: JK1.2, JK2.2, XL1.10
/L_BL: XL1.11, XR1.5
/L_BM: XL1.12, XR1.6
/L_BW: JW1.2, JW2.2, XL1.13
/L_BX: JX1.2, JX2.2, XL1.14
/L_BY: XL1.15, XR1.7
/L_BZ: XL1.16, XR1.8
/L_CJ: JJ1.3, JJ2.3, XL1.17
/L_CK: JK1.3, JK2.3, XL1.18
/L_CL: XL1.19, XR1.9
/L_CM: XL1.20, XR1.10
/L_CW: JW1.3, JW2.3, XL1.21
/L_CX: JX1.3, JX2.3, XL1.22
/L_CY: XL1.23, XR1.11
/L_CZ: XL1.24, XR1.12
/L_DJ: JJ1.4, JJ2.4, XL1.25
/L_DK: JK1.4, JK2.4, XL1.26
/L_DL: XL1.27, XR1.13
/L_DM: XL1.28, XR1.14
/L_DW: JW1.4, JW2.4, XL1.29
/L_DX: JX1.4, JX2.4, XL1.30
/L_DY: XL1.31, XR1.15
/L_DZ: XL1.32, XR1.16
/L_EJ: JJ1.5, JJ2.5, XL1.33
/L_EK: JK1.5, JK2.5, XL1.34
/L_EL: XL1.35, XR1.17
/L_EM: XL1.36, XR1.18
/L_EW: JW1.5, JW2.5, XL1.37
/L_EX: JX1.5, JX2.5, XL1.38
/L_EY: XL1.39, XR1.19
/L_EZ: XL1.40, XR1.20
/L_FJ: JJ1.6, JJ2.6, XL1.41
/L_FK: JK1.6, JK2.6, XL1.42
/L_FL: XL1.43, XR1.21
/L_FM: XL1.44, XR1.22
/L_FW: JW1.6, JW2.6, XL1.45
/L_FX: JX1.6, JX2.6, XL1.46
/L_FY: XL1.47, XR1.23
/L_FZ: XL1.48, XR1.24
/L_GJ: JJ1.7, JJ2.7, XL1.49
/L_GK: JK1.7, JK2.7, XL1.50
/L_GL: XL1.51, XR1.25
/L_GM: XL1.52, XR1.26
/L_GW: JW1.7, JW2.7, XL1.53
/L_GX: JX1.7, JX2.7, XL1.54
/L_GY: XL1.55, XR1.27
/L_GZ: XL1.56, XR1.28
/L_HJ: JJ1.8, JJ2.8, XL1.57
/L_HK: JK1.8, JK2.8, XL1.58
/L_HL: XL1.59, XR1.29
/L_HM: XL1.60, XR1.30
/L_HW: JW1.8, JW2.8, XL1.61
/L_HX: JX1.8, JX2.8, XL1.62
/L_HY: XL1.63, XR1.31
/L_HZ: XL1.64, XR1.32
/L_IJ: JJ1.9, JJ2.9, XL2.1
/L_IK: JK1.9, JK2.9, XL2.2
/L_IL: XL2.3, XR1.33
/L_IM: XL2.4, XR1.34
/L_IW: JW1.9, JW2.9, XL2.5
/L_IX: JX1.9, JX2.9, XL2.6
/L_IY: XL2.7, XR1.35
/L_IZ: XL2.8, XR1.36
/L_JK: JJ1.11, JJ2.11, JK1.10, JK2.10
/L_JL: JJ1.12, JJ2.12, XR1.37
/L_JM: JJ1.13, JJ2.13, XR1.38
/L_JN: JJ1.14, JJ2.14, XL2.9
/L_JO: JJ1.15, JJ2.15, XL2.10
/L_JP: JJ1.16, JJ2.16, XL2.11
/L_JQ: JJ1.17, JJ2.17, XL2.12
/L_JR: JJ1.18, JJ2.18, XL2.13
/L_JS: JJ1.19, JJ2.19, XL2.14
/L_JT: JJ1.20, JJ2.20, XL2.15
/L_JU: JJ1.21, JJ2.21, XL2.16
/L_JV: JJ1.22, JJ2.22, XL2.17
/L_JW: JJ1.23, JJ2.23, JW1.10, JW2.10
/L_JX: JJ1.24, JJ2.24, JX1.10, JX2.10
/L_JY: JJ1.25, JJ2.25, XR1.39
/L_JZ: JJ1.26, JJ2.26, XR1.40
/L_KL: JK1.12, JK2.12, XR1.41
/L_KM: JK1.13, JK2.13, XR1.42
/L_KN: JK1.14, JK2.14, XL2.18
/L_KO: JK1.15, JK2.15, XL2.19
/L_KP: JK1.16, JK2.16, XL2.20
/L_KQ: JK1.17, JK2.17, XL2.21
/L_KR: JK1.18, JK2.18, XL2.22
/L_KS: JK1.19, JK2.19, XL2.23
/L_KT: JK1.20, JK2.20, XL2.24
/L_KU: JK1.21, JK2.21, XL2.25
/L_KV: JK1.22, JK2.22, XL2.26
/L_KW: JK1.23, JK2.23, JW1.11, JW2.11
/L_KX: JK1.24, JK2.24, JX1.11, JX2.11
/L_KY: JK1.25, JK2.25, XR1.43
/L_KZ: JK1.26, JK2.26, XR1.44
/L_LN: XL2.27, XR1.45
/L_LO: XL2.28, XR1.46
/L_LP: XL2.29, XR1.47
/L_LQ: XL2.30, XR1.48
/L_LR: XL2.31, XR1.49
/L_LS: XL2.32, XR1.50
/L_LT: XL2.33, XR1.51
/L_LU: XL2.34, XR1.52
/L_LV: XL2.35, XR1.53
/L_LW: JW1.12, JW2.12, XR1.54
/L_LX: JX1.12, JX2.12, XR1.55
/L_MN: XL2.36, XR1.56
/L_MO: XL2.37, XR1.57
/L_MP: XL2.38, XR1.58
/L_MQ: XL2.39, XR1.59
/L_MR: XL2.40, XR1.60
/L_MS: XL2.41, XR1.61
/L_MT: XL2.42, XR1.62
/L_MU: XL2.43, XR1.63
/L_MV: XL2.44, XR1.64
/L_MW: JW1.13, JW2.13, XR2.1
/L_MX: JX1.13, JX2.13, XR2.2
/L_NW: JW1.14, JW2.14, XL2.45
/L_NX: JX1.14, JX2.14, XL2.46
/L_NY: XL2.47, XR2.3
/L_NZ: XL2.48, XR2.4
/L_OW: JW1.15, JW2.15, XL2.49
/L_OX: JX1.15, JX2.15, XL2.50
/L_OY: XL2.51, XR2.5
/L_OZ: XL2.52, XR2.6
/L_PW: JW1.16, JW2.16, XL2.53
/L_PX: JX1.16, JX2.16, XL2.54
/L_PY: XL2.55, XR2.7
/L_PZ: XL2.56, XR2.8
/L_QW: JW1.17, JW2.17, XL2.57
/L_QX: JX1.17, JX2.17, XL2.58
/L_QY: XL2.59, XR2.9
/L_QZ: XL2.60, XR2.10
/L_RW: JW1.18, JW2.18, XL2.61
/L_RX: JX1.18, JX2.18, XL2.62
/L_RY: XL2.63, XR2.11
/L_RZ: XL2.64, XR2.12
/L_SW: JW1.19, JW2.19, XL3.1
/L_SX: JX1.19, JX2.19, XL3.2
/L_SY: XL3.3, XR2.13
/L_SZ: XL3.4, XR2.14
/L_TW: JW1.20, JW2.20, XL3.5
/L_TX: JX1.20, JX2.20, XL3.6
/L_TY: XL3.7, XR2.15
/L_TZ: XL3.8, XR2.16
/L_UW: JW1.21, JW2.21, XL3.9
/L_UX: JX1.21, JX2.21, XL3.10
/L_UY: XL3.11, XR2.17
/L_UZ: XL3.12, XR2.18
/L_VW: JW1.22, JW2.22, XL3.13
/L_VX: JX1.22, JX2.22, XL3.14
/L_VY: XL3.15, XR2.19
/L_VZ: XL3.16, XR2.20
/L_WX: JW1.24, JW2.24, JX1.23, JX2.23
/L_WY: JW1.25, JW2.25, XR2.21
/L_WZ: JW1.26, JW2.26, XR2.22
/L_XY: JX1.25, JX2.25, XR2.23
/L_XZ: JX1.26, JX2.26, XR2.24
/S_J: JJ1.10, JJ2.10
/S_K: JK1.11, JK2.11
/S_W: JW1.23, JW2.23
/S_X: JX1.24, JX2.24

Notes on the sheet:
Diagonal board D4 of 5 - letters J W K X (4 letters, 8 jacks). Link net L_XY joins wire Y of letter X and wire X of letter Y on all four jacks of the two letters; S_X = own wire of letter X. Junction headers: 3 per boundary, ribbon pin n <-> pin n; links sorted by (X,Y) take connector (i // 64 + 1)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

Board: 4 copper layers, 20 parts (6 on the bottom side), 172 nets, no tracks yet.
